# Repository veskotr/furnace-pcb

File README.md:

# Furnace Controller PCB

Hardware revisions are kept side by side:

- `Furnace_Controller_V1/` — the original 99-footprint design, last produced in June 2026.
- `Furnace_Controller_V2/` — the active 125-footprint revision, including the expanded functional-sheet hierarchy and TI footprint corrections.

Open the `Furnace_Controller.kicad_pro` inside the revision you intend to edit.
Shared third-party symbols and footprints live in `libraries/Symbols/`; each revision's
library-table files resolve these assets using project-relative paths.

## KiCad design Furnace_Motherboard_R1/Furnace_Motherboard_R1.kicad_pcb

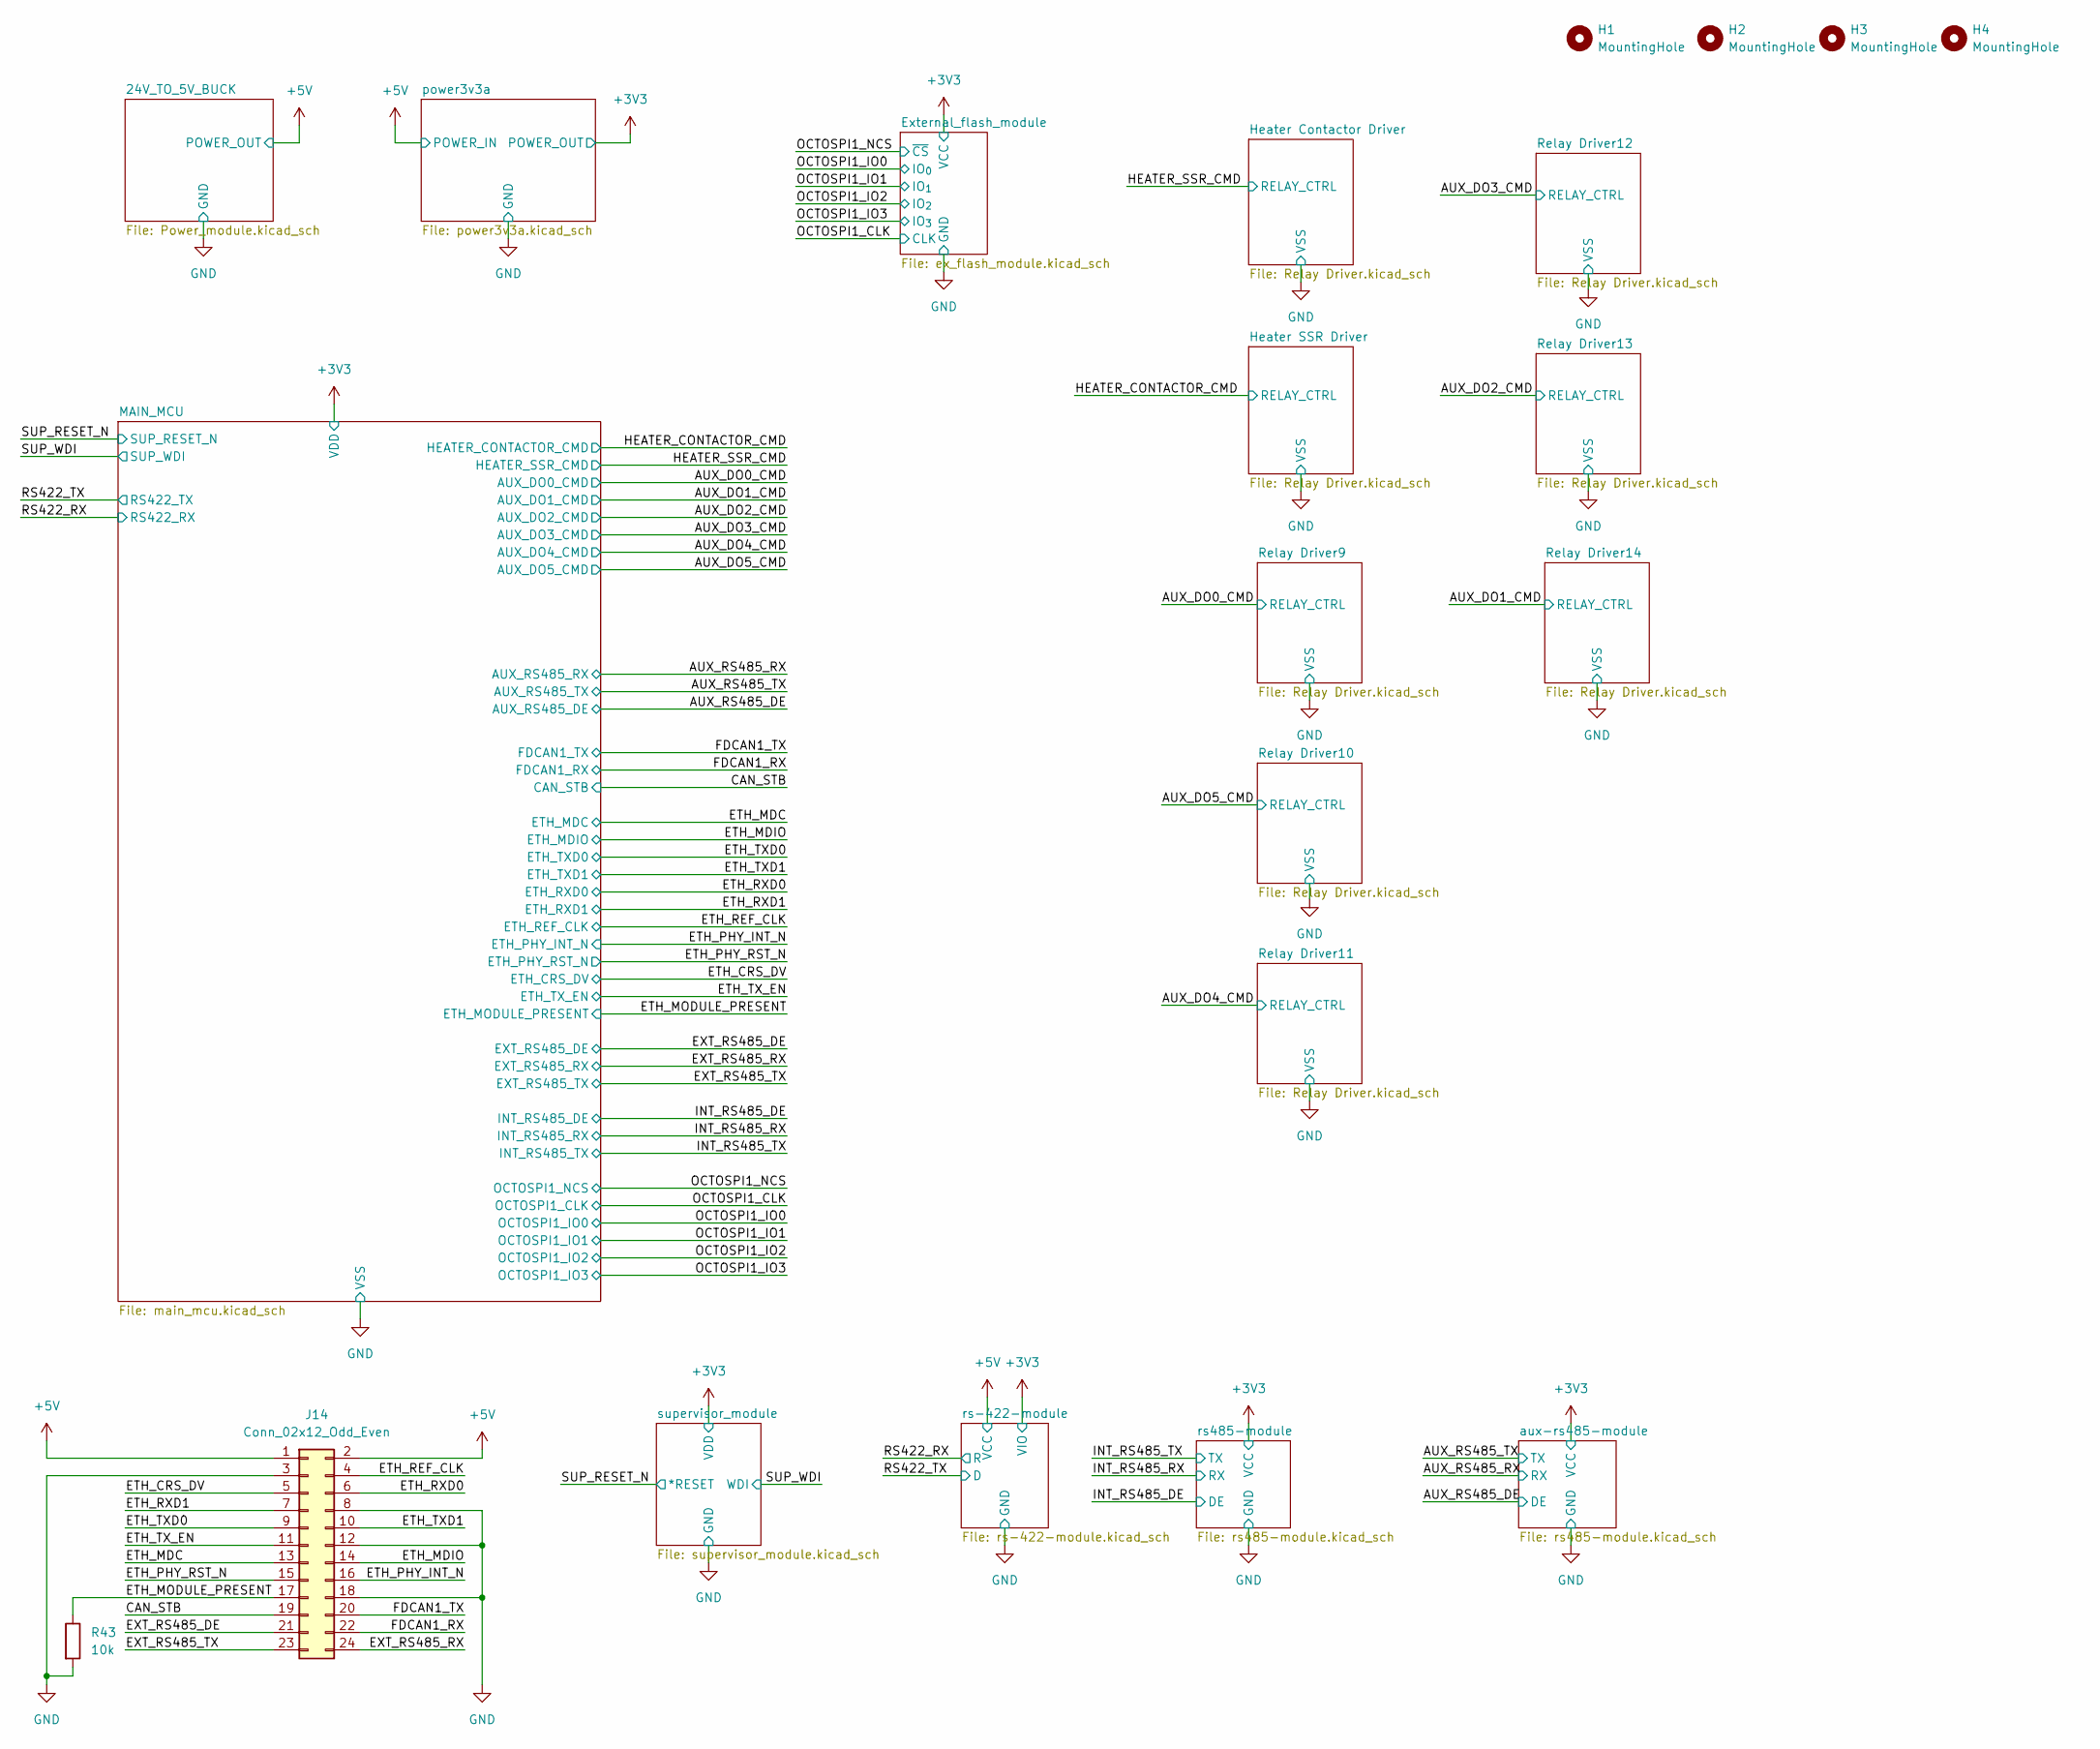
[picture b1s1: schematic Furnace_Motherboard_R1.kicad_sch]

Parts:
H1, H2, H3, H4: MountingHole; MountingHole_3.2mm_M3
J14: Conn_02x12_Odd_Even; PinSocket_2x12_P2.54mm_Vertical
R43: 10k; R_0603_1608Metric

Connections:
+5V: J14.1, J14.2; also elsewhere on the board
/CAN_STB: J14.19; also elsewhere on the board
/ETH_CRS_DV: J14.5; also elsewhere on the board
/ETH_MDC: J14.13; also elsewhere on the board
/ETH_MDIO: J14.14; also elsewhere on the board
/ETH_MODULE_PRESENT: J14.17, R43.1; also elsewhere on the board
/ETH_PHY_INT_N: J14.16; also elsewhere on the board
/ETH_PHY_RST_N: J14.15; also elsewhere on the board
/ETH_REF_CLK: J14.4; also elsewhere on the board
/ETH_RXD0: J14.6; also elsewhere on the board
/ETH_RXD1: J14.7; also elsewhere on the board
/ETH_TXD0: J14.9; also elsewhere on the board
/ETH_TXD1: J14.10; also elsewhere on the board
/ETH_TX_EN: J14.11; also elsewhere on the board
/EXT_RS485_DE: J14.21; also elsewhere on the board
/EXT_RS485_RX: J14.24; also elsewhere on the board
/EXT_RS485_TX: J14.23; also elsewhere on the board
/FDCAN1_RX: J14.22; also elsewhere on the board
/FDCAN1_TX: J14.20; also elsewhere on the board
GND: J14.3, J14.8, J14.12, J14.18, R43.2; also elsewhere on the board

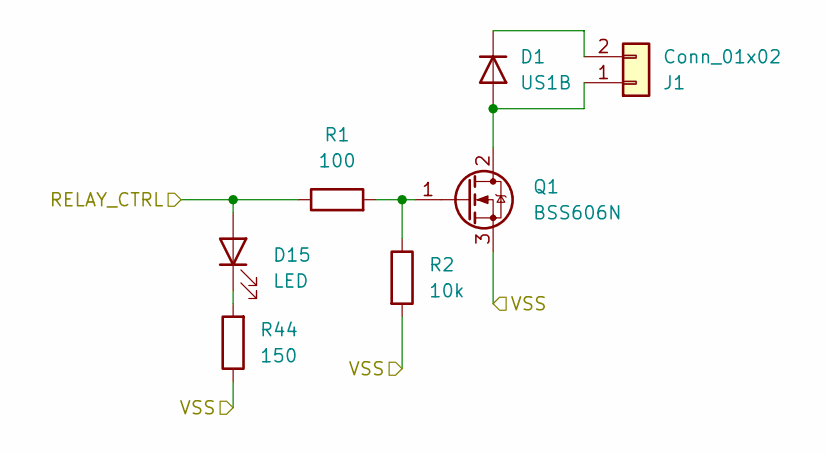
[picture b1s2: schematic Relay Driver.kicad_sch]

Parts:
D1: US1B; D_SMA
D15: LED; LED_0603_1608Metric
J1: Conn_01x02; PhoenixContact_MC_1,5_2-G-3.5_1x02_P3.50mm_Horizontal
Q1: BSS606N; Q_SOT-89
R1: 100; R_0603_1608Metric
R2: 10k; R_0603_1608Metric
R44: 150; R_0603_1608Metric

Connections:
/AUX_DO3_CMD: D15.2 (A), R1.1; also elsewhere on the board
GND: Q1.3 (S), R2.2, R44.1; also elsewhere on the board
unnamed: D1.2 (A), J1.1, Q1.2 (D)
unnamed: D1.1 (K), J1.2
unnamed: D15.1 (K), R44.2
unnamed: Q1.1 (G), R1.2, R2.1

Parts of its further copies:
D2, D6, D7, D8, D9, D10, D11: US1B; D_SMA
D16, D17, D18, D19, D20, D21, D22: LED; LED_0603_1608Metric
J2, J6, J7, J8, J9, J10, J11: Conn_01x02; PhoenixContact_MC_1,5_2-G-3.5_1x02_P3.50mm_Horizontal
Q2, Q3, Q4, Q5, Q6, Q7, Q8: BSS606N; Q_SOT-89
R3, R18, R20, R22, R24, R26, R28: 100; R_0603_1608Metric
R4, R19, R21, R23, R25, R27, R29: 10k; R_0603_1608Metric
R45, R46, R47, R48, R49, R50, R51: 150; R_0603_1608Metric

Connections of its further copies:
/AUX_DO0_CMD: D20.2 (A), R24.1; also elsewhere on the board
/AUX_DO1_CMD: D19.2 (A), R22.1; also elsewhere on the board
/AUX_DO2_CMD: D16.2 (A), R3.1; also elsewhere on the board
/AUX_DO4_CMD: D22.2 (A), R28.1; also elsewhere on the board
/AUX_DO5_CMD: D21.2 (A), R26.1; also elsewhere on the board
/HEATER_CONTACTOR_CMD: D18.2 (A), R20.1; also elsewhere on the board
/HEATER_SSR_CMD: D17.2 (A), R18.1; also elsewhere on the board
GND: Q2.3 (S), Q3.3 (S), Q4.3 (S), Q5.3 (S), Q6.3 (S), Q7.3 (S), Q8.3 (S), R4.2, R19.2, R21.2, R23.2, R25.2, R27.2, R29.2, R45.1, R46.1, R47.1, R48.1, R49.1, R50.1, R51.1; also elsewhere on the board
unnamed: D2.2 (A), J2.1, Q2.2 (D)
unnamed: D2.1 (K), J2.2
unnamed: D6.2 (A), J6.1, Q3.2 (D)
unnamed: D6.1 (K), J6.2
unnamed: D7.2 (A), J7.1, Q4.2 (D)
unnamed: D7.1 (K), J7.2
unnamed: D8.2 (A), J8.1, Q5.2 (D)
unnamed: D8.1 (K), J8.2
unnamed: D9.2 (A), J9.1, Q6.2 (D)
unnamed: D9.1 (K), J9.2
unnamed: D10.2 (A), J10.1, Q7.2 (D)
unnamed: D10.1 (K), J10.2
unnamed: D11.2 (A), J11.1, Q8.2 (D)
unnamed: D11.1 (K), J11.2
unnamed: D16.1 (K), R45.2
unnamed: D17.1 (K), R46.2
unnamed: D18.1 (K), R47.2
unnamed: D19.1 (K), R48.2
unnamed: D20.1 (K), R49.2
unnamed: D21.1 (K), R50.2
unnamed: D22.1 (K), R51.2
unnamed: Q2.1 (G), R3.2, R4.1
unnamed: Q3.1 (G), R18.2, R19.1
unnamed: Q4.1 (G), R20.2, R21.1
unnamed: Q5.1 (G), R22.2, R23.1
unnamed: Q6.1 (G), R24.2, R25.1
unnamed: Q7.1 (G), R26.2, R27.1
unnamed: Q8.1 (G), R28.2, R29.1

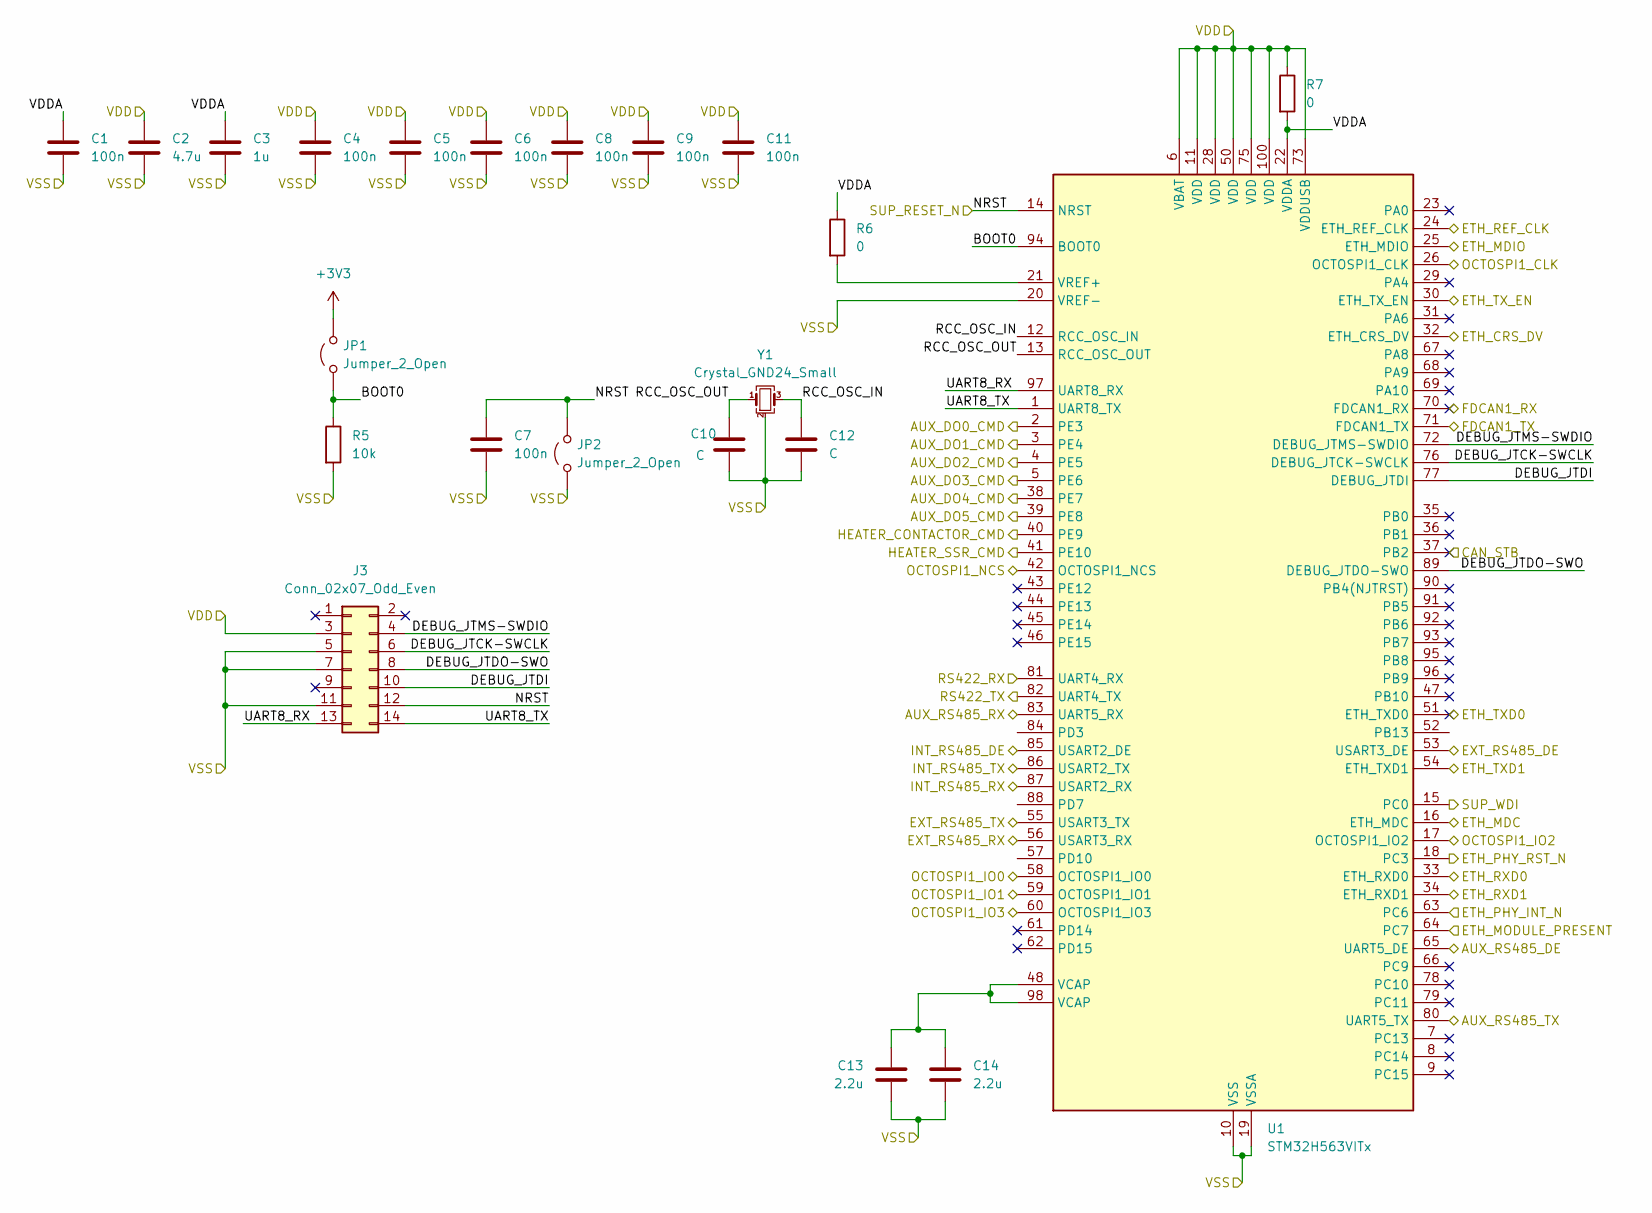
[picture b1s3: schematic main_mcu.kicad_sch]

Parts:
C1, C4, C5, C6, C7, C8, C9, C11: 100n; C_0603_1608Metric
C2: 4.7u; C_0805_2012Metric
C3: 1u; C_0603_1608Metric
C10, C12: C; C_0603_1608Metric
C13, C14: 2.2u; C_0805_2012Metric
J3: Conn_02x07_Odd_Even; PinHeader_2x07_P1.27mm_Vertical
JP1, JP2: Jumper_2_Open; TestPoint_2Pads_Pitch2.54mm_Drill0.8mm
R5: 10k; R_0603_1608Metric
R6, R7: 0; R_0603_1608Metric
U1: STM32H563VITx; LQFP-100_14x14mm_P0.5mm
Y1: Crystal_GND24_Small; Crystal_SMD_3225-4Pin_3.2x2.5mm

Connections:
+3V3: C2.1, C4.1, C5.1, C6.1, C8.1, C9.1, C11.1, J3.3, JP1.2 (B), R7.1, U1.6 (VBAT), U1.11 (VDD), U1.28 (VDD), U1.50 (VDD), U1.73 (VDDUSB), U1.75 (VDD), U1.100 (VDD); also elsewhere on the board
/AUX_DO0_CMD: U1.2 (PE3); also elsewhere on the board
/AUX_DO1_CMD: U1.3 (PE4); also elsewhere on the board
/AUX_DO2_CMD: U1.4 (PE5); also elsewhere on the board
/AUX_DO3_CMD: U1.5 (PE6); also elsewhere on the board
/AUX_DO4_CMD: U1.38 (PE7); also elsewhere on the board
/AUX_DO5_CMD: U1.39 (PE8); also elsewhere on the board
/AUX_RS485_DE: U1.65 (UART5_DE); also elsewhere on the board
/AUX_RS485_RX: U1.83 (UART5_RX); also elsewhere on the board
/AUX_RS485_TX: U1.80 (UART5_TX); also elsewhere on the board
/CAN_STB: U1.37 (PB2); also elsewhere on the board
/ETH_CRS_DV: U1.32 (ETH_CRS_DV); also elsewhere on the board
/ETH_MDC: U1.16 (ETH_MDC); also elsewhere on the board
/ETH_MDIO: U1.25 (ETH_MDIO); also elsewhere on the board
/ETH_MODULE_PRESENT: U1.64 (PC7); also elsewhere on the board
/ETH_PHY_INT_N: U1.63 (PC6); also elsewhere on the board
/ETH_PHY_RST_N: U1.18 (PC3); also elsewhere on the board
/ETH_REF_CLK: U1.24 (ETH_REF_CLK); also elsewhere on the board
/ETH_RXD0: U1.33 (ETH_RXD0); also elsewhere on the board
/ETH_RXD1: U1.34 (ETH_RXD1); also elsewhere on the board
/ETH_TXD0: U1.51 (ETH_TXD0); also elsewhere on the board
/ETH_TXD1: U1.54 (ETH_TXD1); also elsewhere on the board
/ETH_TX_EN: U1.30 (ETH_TX_EN); also elsewhere on the board
/EXT_RS485_DE: U1.53 (USART3_DE); also elsewhere on the board
/EXT_RS485_RX: U1.56 (USART3_RX); also elsewhere on the board
/EXT_RS485_TX: U1.55 (USART3_TX); also elsewhere on the board
/FDCAN1_RX: U1.70 (FDCAN1_RX); also elsewhere on the board
/FDCAN1_TX: U1.71 (FDCAN1_TX); also elsewhere on the board
/HEATER_CONTACTOR_CMD: U1.40 (PE9); also elsewhere on the board
/HEATER_SSR_CMD: U1.41 (PE10); also elsewhere on the board
/INT_RS485_DE: U1.85 (USART2_DE); also elsewhere on the board
/INT_RS485_RX: U1.87 (USART2_RX); also elsewhere on the board
/INT_RS485_TX: U1.86 (USART2_TX); also elsewhere on the board
/MAIN_MCU/BOOT0: JP1.1 (A), R5.1, U1.94 (BOOT0)
/MAIN_MCU/DEBUG_JTCK-SWCLK: J3.6, U1.76 (DEBUG_JTCK-SWCLK)
/MAIN_MCU/DEBUG_JTDI: J3.10, U1.77 (DEBUG_JTDI)
/MAIN_MCU/DEBUG_JTDO-SWO: J3.8, U1.89 (DEBUG_JTDO-SWO)
/MAIN_MCU/DEBUG_JTMS-SWDIO: J3.4, U1.72 (DEBUG_JTMS-SWDIO)
/MAIN_MCU/RCC_OSC_IN: C12.1, U1.12 (RCC_OSC_IN), Y1.3
/MAIN_MCU/RCC_OSC_OUT: C10.1, U1.13 (RCC_OSC_OUT), Y1.1
/MAIN_MCU/UART8_RX: J3.13, U1.97 (UART8_RX)
/MAIN_MCU/UART8_TX: J3.14, U1.1 (UART8_TX)
/MAIN_MCU/VDDA: C1.1, C3.1, R6.1, R7.2, U1.22 (VDDA)
/OCTOSPI1_CLK: U1.26 (OCTOSPI1_CLK); also elsewhere on the board
/OCTOSPI1_IO0: U1.58 (OCTOSPI1_IO0); also elsewhere on the board
/OCTOSPI1_IO1: U1.59 (OCTOSPI1_IO1); also elsewhere on the board
/OCTOSPI1_IO2: U1.17 (OCTOSPI1_IO2); also elsewhere on the board
/OCTOSPI1_IO3: U1.60 (OCTOSPI1_IO3); also elsewhere on the board
/OCTOSPI1_NCS: U1.42 (OCTOSPI1_NCS); also elsewhere on the board
/RS422_RX: U1.81 (UART4_RX); also elsewhere on the board
/RS422_TX: U1.82 (UART4_TX); also elsewhere on the board
/SUP_RESET_N: C7.1, J3.12, JP2.2 (B), U1.14 (NRST); also elsewhere on the board
/SUP_WDI: U1.15 (PC0); also elsewhere on the board
GND: C1.2, C2.2, C3.2, C4.2, C5.2, C6.2, C7.2, C8.2, C9.2, C10.2, C11.2, C12.2, C13.2, C14.2, J3.5, J3.7, J3.11, JP2.1 (A), R5.2, U1.10 (VSS), U1.19 (VSSA), U1.20 (VREF-), U1.27 (VSS), U1.49 (VSS), U1.74 (VSS), U1.99 (VSS), Y1.2 (G), Y1.4 (G); also elsewhere on the board
unnamed: C13.1, C14.1, U1.48 (VCAP), U1.98 (VCAP)
unnamed: R6.2, U1.21 (VREF+)

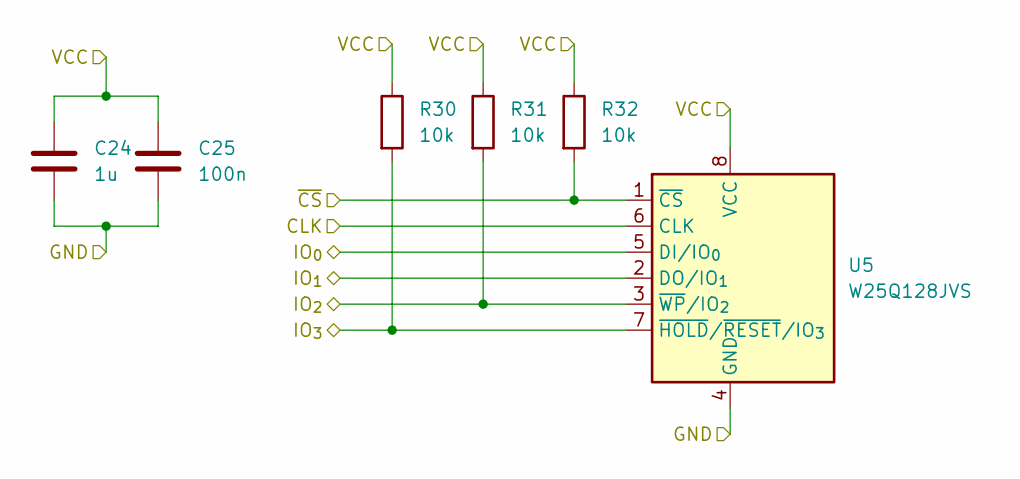
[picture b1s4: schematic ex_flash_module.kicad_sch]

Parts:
C24: 1u; C_0603_1608Metric
C25: 100n; C_0603_1608Metric
R30, R31, R32: 10k; R_0603_1608Metric
U5: W25Q128JVS; SOIC-8_5.3x5.3mm_P1.27mm

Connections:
+3V3: C24.1, C25.1, R30.1, R31.1, R32.1, U5.8 (VCC); also elsewhere on the board
/OCTOSPI1_CLK: U5.6 (CLK); also elsewhere on the board
/OCTOSPI1_IO0: U5.5 (DI/IO_{0}); also elsewhere on the board
/OCTOSPI1_IO1: U5.2 (DO/IO_{1}); also elsewhere on the board
/OCTOSPI1_IO2: R31.2, U5.3 (~WP/IO_{2}); also elsewhere on the board
/OCTOSPI1_IO3: R30.2, U5.7 (~HOLD/~RESET/IO_{3}); also elsewhere on the board
/OCTOSPI1_NCS: R32.2, U5.1 (~CS); also elsewhere on the board
GND: C24.2, C25.2, U5.4 (GND); also elsewhere on the board

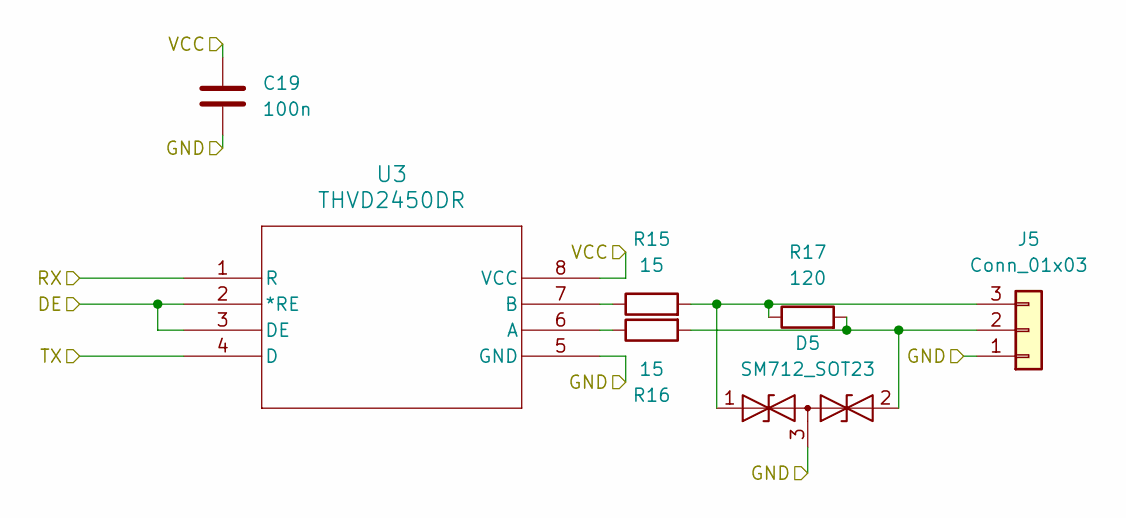
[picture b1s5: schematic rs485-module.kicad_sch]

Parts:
C19: 100n; C_0603_1608Metric
D5: SM712_SOT23; SOT-23
J5: Conn_01x03; PhoenixContact_MC_1,5_3-G-3.5_1x03_P3.50mm_Horizontal
R15, R16: 15; R_0603_1608Metric
R17: 120; R_0603_1608Metric
U3: THVD2450DR; SOIC-8_3.9x4.9mm_P1.27mm

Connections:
+3V3: C19.1, U3.8 (VCC); also elsewhere on the board
/INT_RS485_DE: U3.2 (*RE), U3.3 (DE); also elsewhere on the board
/INT_RS485_RX: U3.1 (R); also elsewhere on the board
/INT_RS485_TX: U3.4 (D); also elsewhere on the board
GND: C19.2, D5.3 (common), J5.1, U3.5 (GND); also elsewhere on the board
unnamed: D5.1 (A1), J5.3, R15.2, R17.1
unnamed: D5.2 (A2), J5.2, R16.2, R17.2
unnamed: R16.1, U3.6 (A)
unnamed: R15.1, U3.7 (B)

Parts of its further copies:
C29: 100n; C_0603_1608Metric
D12: SM712_SOT23; SOT-23
J12: Conn_01x03; PhoenixContact_MC_1,5_3-G-3.5_1x03_P3.50mm_Horizontal
R35, R36: 15; R_0603_1608Metric
R37: 120; R_0603_1608Metric
U7: THVD2450DR; SOIC-8_3.9x4.9mm_P1.27mm

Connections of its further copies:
+3V3: C29.1, U7.8 (VCC); also elsewhere on the board
/AUX_RS485_DE: U7.2 (*RE), U7.3 (DE); also elsewhere on the board
/AUX_RS485_RX: U7.1 (R); also elsewhere on the board
/AUX_RS485_TX: U7.4 (D); also elsewhere on the board
GND: C29.2, D12.3 (common), J12.1, U7.5 (GND); also elsewhere on the board
unnamed: D12.1 (A1), J12.3, R35.2, R37.1
unnamed: D12.2 (A2), J12.2, R36.2, R37.2
unnamed: R36.1, U7.6 (A)
unnamed: R35.1, U7.7 (B)

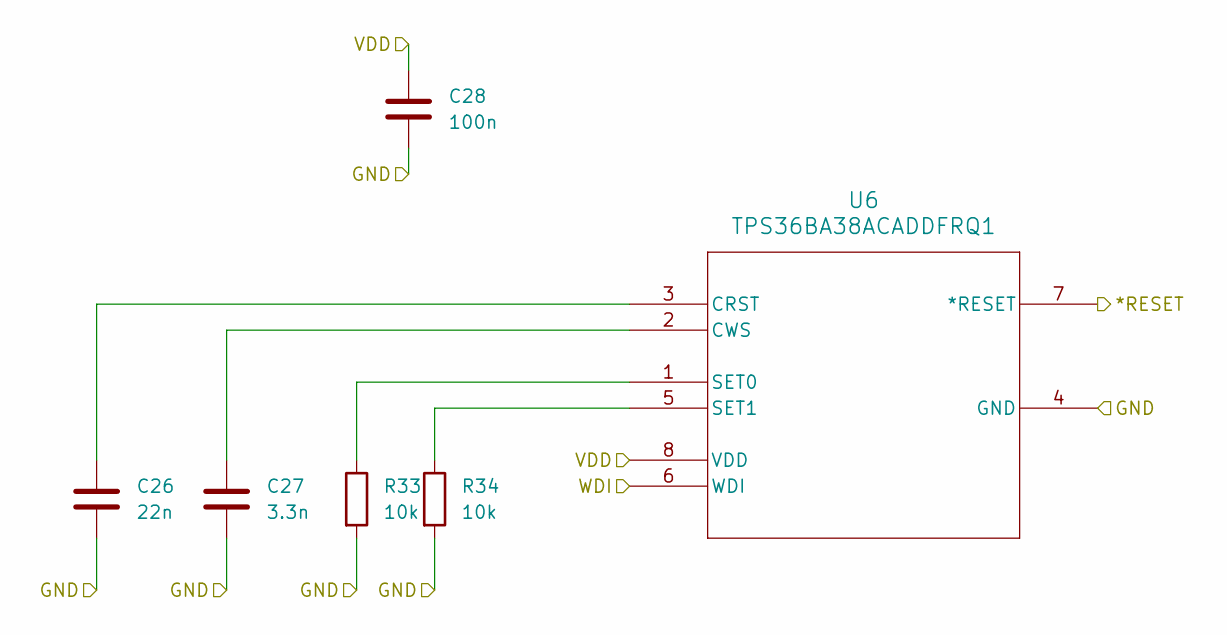
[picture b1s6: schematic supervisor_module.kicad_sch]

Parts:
C26: 22n; C_0603_1608Metric
C27: 3.3n; C_0603_1608Metric
C28: 100n; C_0603_1608Metric
R33, R34: 10k; R_0603_1608Metric
U6: TPS36BA38ACADDFRQ1; SOT-23-THIN-8_DDF_TEX

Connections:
+3V3: C28.1, U6.8 (VDD); also elsewhere on the board
/SUP_RESET_N: U6.7 (*RESET); also elsewhere on the board
/SUP_WDI: U6.6 (WDI); also elsewhere on the board
GND: C26.2, C27.2, C28.2, R33.2, R34.2, U6.4 (GND); also elsewhere on the board
unnamed: C26.1, U6.3 (CRST)
unnamed: C27.1, U6.2 (CWS)
unnamed: R33.1, U6.1 (SET0)
unnamed: R34.1, U6.5 (SET1)

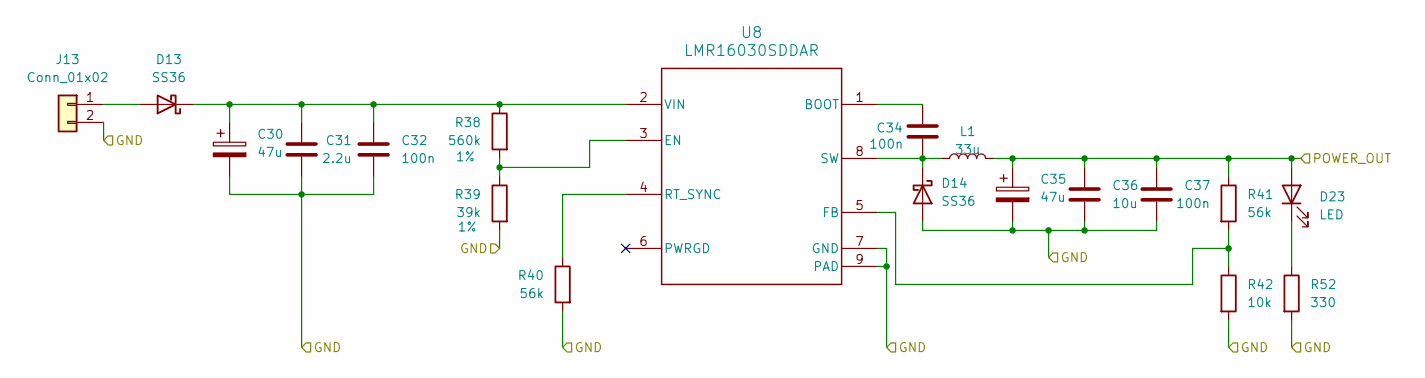
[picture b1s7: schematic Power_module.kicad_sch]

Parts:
C30, C35: 47u; CP_Radial_D6.3mm_P2.50mm
C31: 2.2u; C_0805_2012Metric
C32, C34, C37: 100n; C_0603_1608Metric
C36: 10u; C_0805_2012Metric
D13, D14: SS36; D_SMA
D23: LED; LED_0603_1608Metric
J13: Conn_01x02; PhoenixContact_MC_1,5_2-G-3.5_1x02_P3.50mm_Horizontal
L1: 33u; L_6.3x6.3_H3
R38: 560k; R_0603_1608Metric; Tolerance 1%
R39: 39k; R_0603_1608Metric; Tolerance 1%
R40, R41: 56k; R_0603_1608Metric
R42: 10k; R_0603_1608Metric
R52: 330; R_0603_1608Metric
U8: LMR16030SDDAR; SOIC-8-1EP_3.9x4.9mm_P1.27mm_EP2.29x3mm

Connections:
+5V: C35.1, C36.1, C37.1, D23.2 (A), L1.2, R41.1; also elsewhere on the board
GND: C30.2, C31.2, C32.2, C35.2, C36.2, C37.2, D14.2 (A), J13.2, R39.2, R40.2, R42.2, R52.2, U8.7 (GND), U8.9 (PAD); also elsewhere on the board
unnamed: D13.2 (A), J13.1
unnamed: C30.1, C31.1, C32.1, D13.1 (K), R38.1, U8.2 (VIN)
unnamed: C34.2, D14.1 (K), L1.1, U8.8 (SW)
unnamed: D23.1 (K), R52.1
unnamed: C34.1, U8.1 (BOOT)
unnamed: R38.2, R39.1, U8.3 (EN)
unnamed: R41.2, R42.1, U8.5 (FB)
unnamed: R40.1, U8.4 (RT_SYNC)

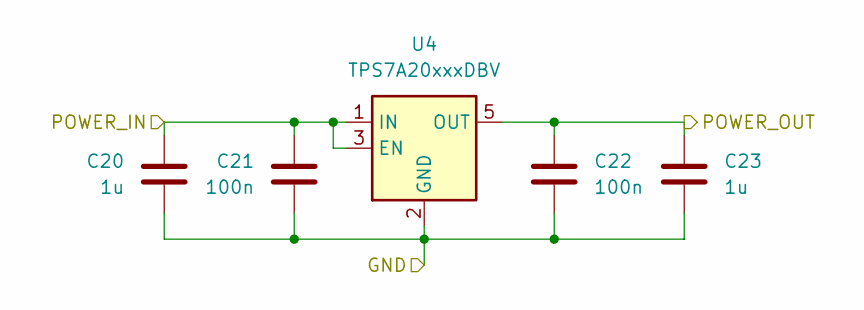
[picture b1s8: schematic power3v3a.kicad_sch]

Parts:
C20, C23: 1u; C_0603_1608Metric
C21, C22: 100n; C_0603_1608Metric
U4: TPS7A20xxxDBV; SOT-23-5

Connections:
+3V3: C22.1, C23.1, U4.5 (OUT); also elsewhere on the board
+5V: C20.1, C21.1, U4.1 (IN), U4.3 (EN); also elsewhere on the board
GND: C20.2, C21.2, C22.2, C23.2, U4.2 (GND); also elsewhere on the board

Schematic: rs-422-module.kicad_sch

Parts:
C15, C16: 100n; C_0603_1608Metric
C17, C18: 1u; C_0805_2012Metric
D3, D4: SM712_SOT23; SOT-23
J4: Conn_01x05; PhoenixContact_MC_1,5_5-G-3.5_1x05_P3.50mm_Horizontal
R8, R10, R11: 10k; R_0603_1608Metric
R9: 0; R_0603_1608Metric
R12: 120; R_0603_1608Metric
R13, R14: 15; R_0603_1608Metric
U2: PTHVD2452VDR; SOIC-14_L8.7-W3.9-P1.27-LS6.0-BL

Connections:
+3V3: C15.1, C17.1, R8.1, R10.1, U2.1 (VIO); also elsewhere on the board
+5V: C16.1, C18.1, U2.14 (VCC); also elsewhere on the board
/RS422_RX: U2.2 (R); also elsewhere on the board
/RS422_TX: U2.5 (D); also elsewhere on the board
/rs-422-module/A: D3.1 (A1), J4.5, R12.1, U2.12 (A)
/rs-422-module/B: D3.2 (A2), J4.4, R12.2, U2.11 (B)
/rs-422-module/Y: D4.2 (A2), J4.2, R13.1
/rs-422-module/Z: D4.1 (A1), J4.3, R14.1
GND: C15.2, C16.2, C17.2, C18.2, D3.3 (common), D4.3 (common), J4.1, R9.2, R11.2, U2.6 (GND); also elsewhere on the board
unnamed: R11.1, U2.3 (*RE)
unnamed: R10.2, U2.4 (DE)
unnamed: R8.2, R9.1, U2.8 (SLR)
unnamed: R13.2, U2.9 (Y)
unnamed: R14.2, U2.10 (Z)

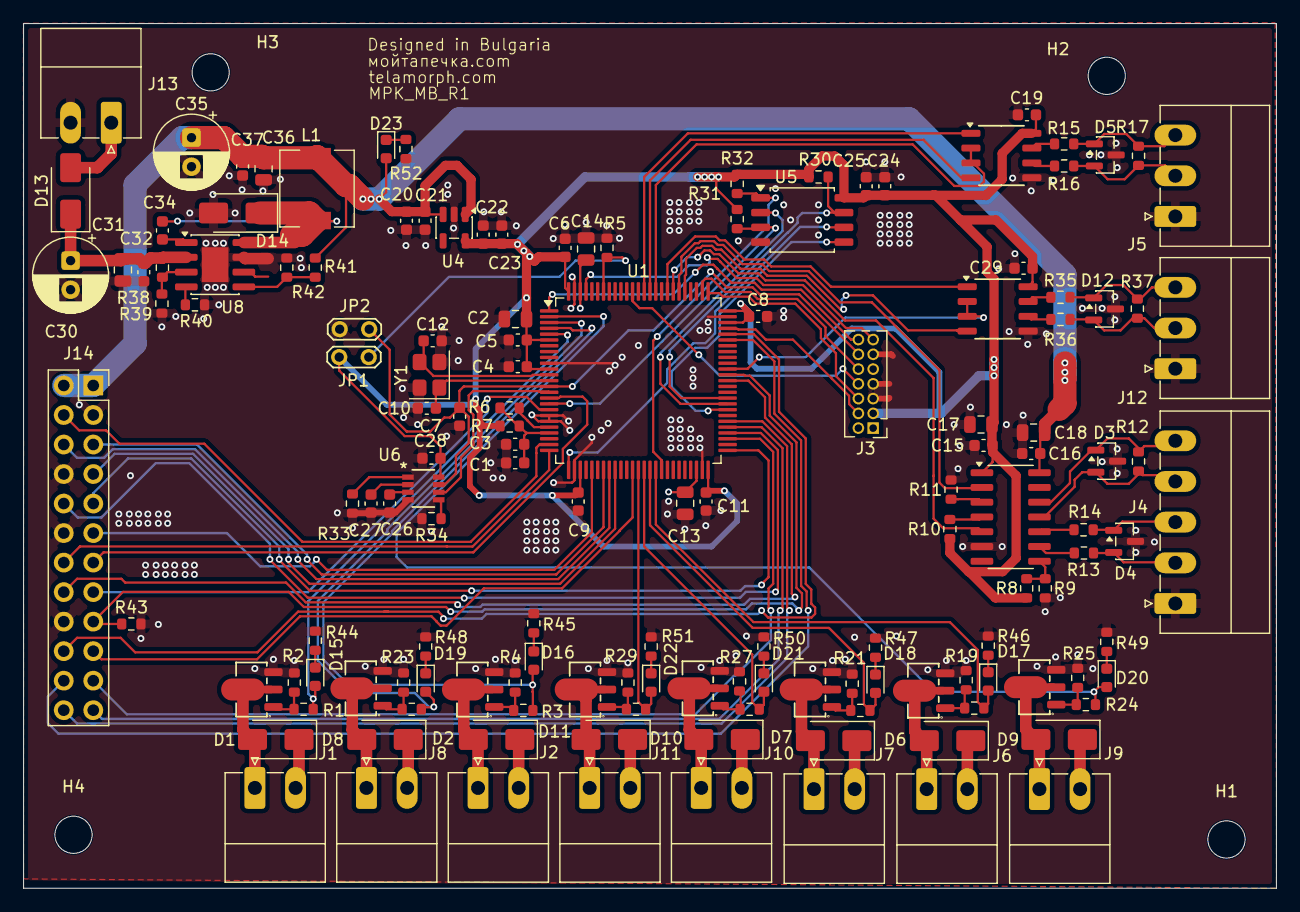
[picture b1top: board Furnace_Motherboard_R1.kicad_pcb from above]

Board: 4 copper layers, 107.8 x 74.4 mm, 149 parts (0 on the bottom side), 118 nets.

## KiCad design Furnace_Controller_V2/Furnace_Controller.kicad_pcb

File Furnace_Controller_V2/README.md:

# Furnace Controller V2

Open `Furnace_Controller.kicad_pro` as the project entry point.

The root schematic is the system sheet. Functional sheets are named by their
role (power conversion, communications, supervision, I/O, Ethernet, and relay
drivers). Repeated relay and 3.3 V regulator channels intentionally share a
single child-sheet source.

Project-local TI symbols and footprints are declared in `sym-lib-table` and
`fp-lib-table`; their source files live in `../libraries/Symbols/`. Child
schematics live in `sheets/`; generated Gerbers and assembly outputs live in
`fabrication/`, while PDFs and 3D exports live in `documentation/`.

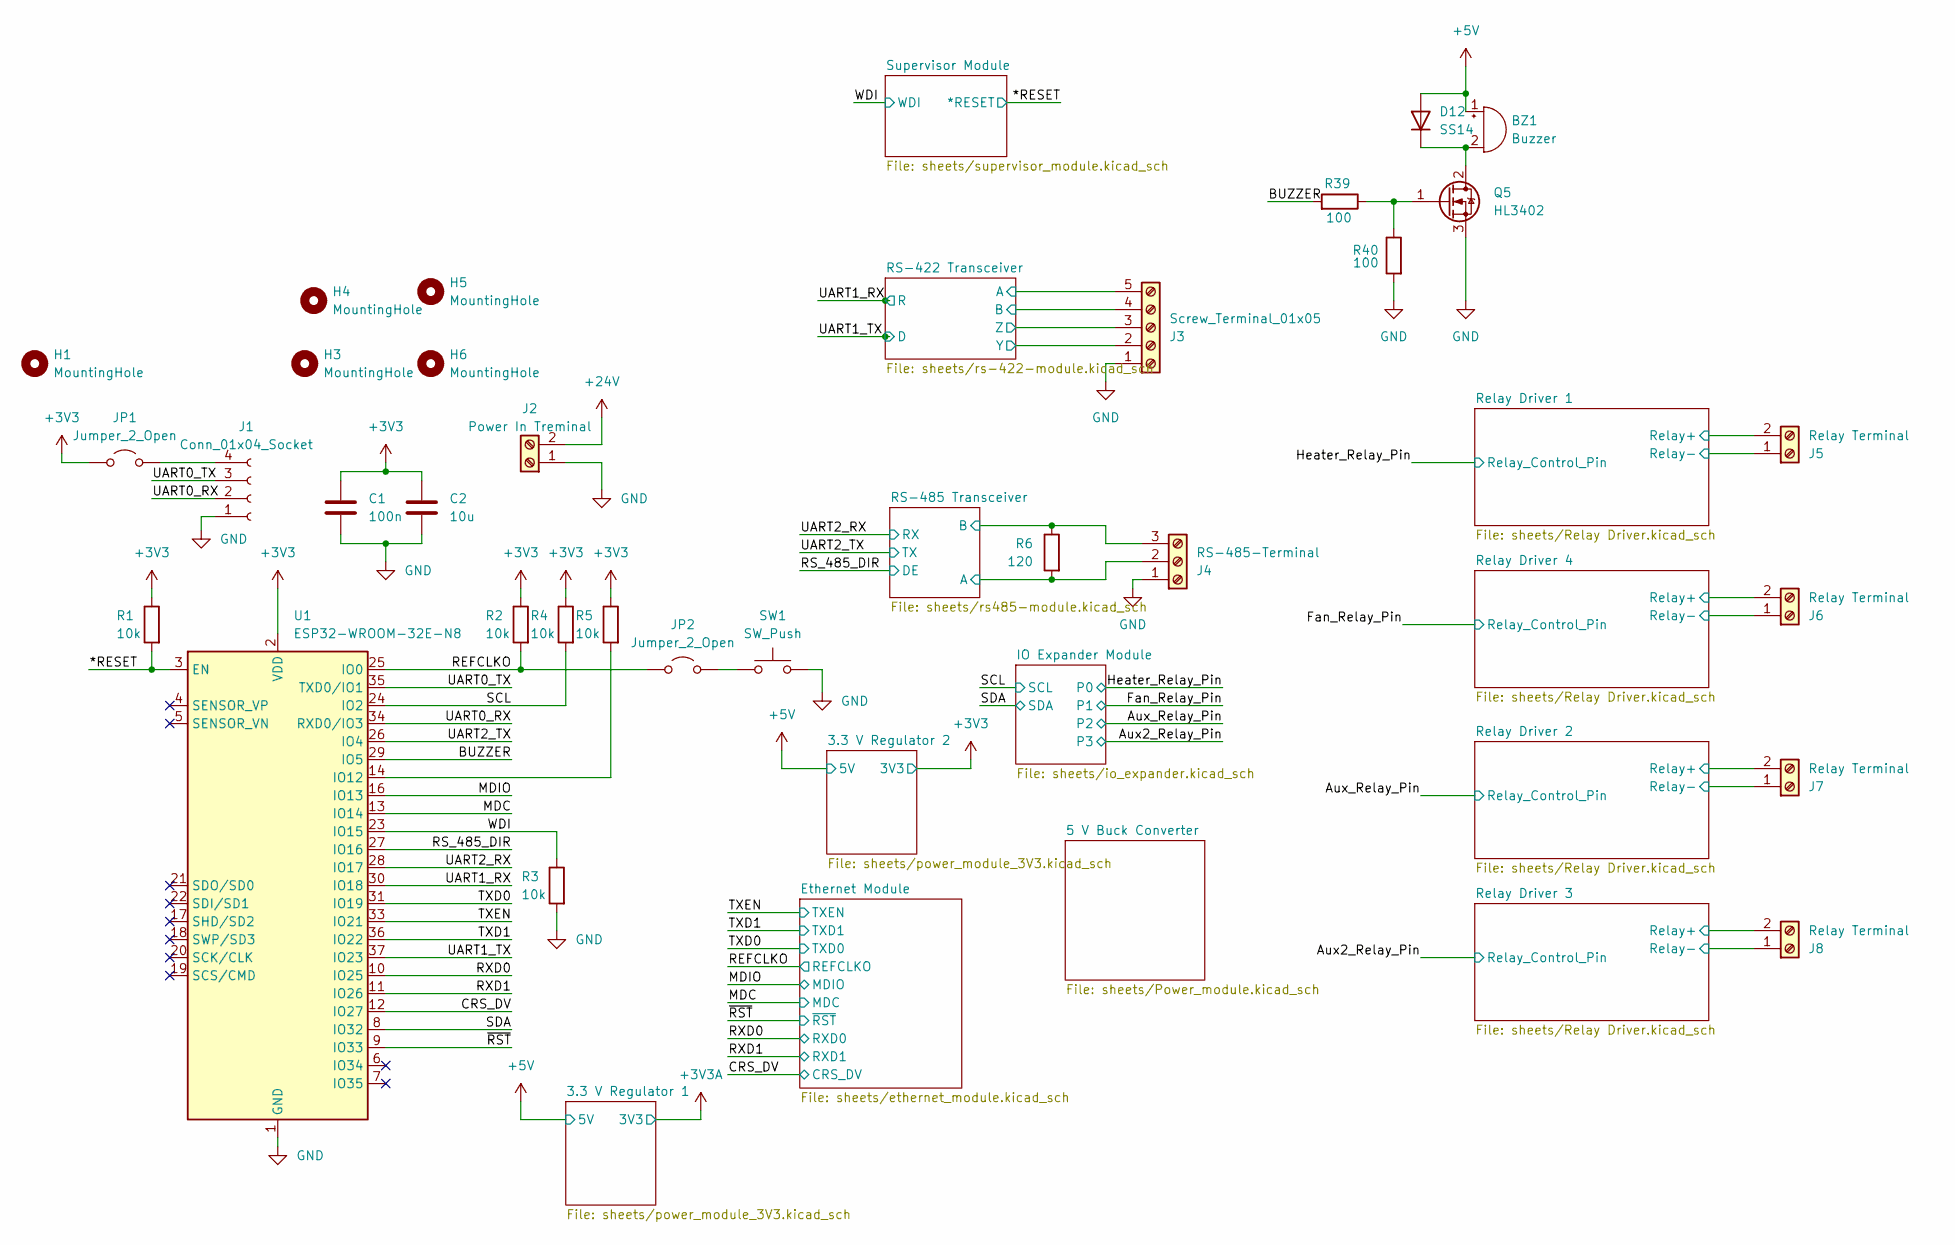
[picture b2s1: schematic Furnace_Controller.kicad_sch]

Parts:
BZ1: Buzzer; Buzzer_15x7.5RM7.6
C1: 100n; C_0603_1608Metric
C2: 10u; C_0805_2012Metric
D12: SS14; D_SOD-123
H1, H3, H4, H6: MountingHole; MountingHole_3.2mm_M3
H5: MountingHole; MountingHole_2.2mm_M2
J1: Conn_01x04_Socket; PinHeader_1x04_P2.54mm_Vertical
J2: Power In Treminal; PhoenixContact_MC_1,5_2-G-3.5_1x02_P3.50mm_Horizontal
J3: Screw_Terminal_01x05; PhoenixContact_MC_1,5_5-G-3.5_1x05_P3.50mm_Horizontal
J4: RS-485-Terminal; PhoenixContact_MC_1,5_3-G-3.5_1x03_P3.50mm_Horizontal
J5, J6, J7, J8: Relay Terminal; PhoenixContact_MC_1,5_2-G-3.5_1x02_P3.50mm_Horizontal
JP1, JP2: Jumper_2_Open; TestPoint_2Pads_Pitch2.54mm_Drill0.8mm
Q5: HL3402; Q_SOT-23
R1, R2, R3, R4, R5: 10k; R_0603_1608Metric
R6: 120; R_0603_1608Metric
R39, R40: 100; R_0603_1608Metric
SW1: SW_Push; SW_PUSH_6mm_H4.3mm
U1: ESP32-WROOM-32E-N8; ESP32-WROOM-32

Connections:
+3V3: C1.1, C2.1, JP1.1 (A), R1.1, R2.1, R4.1, R5.1, U1.2 (VDD); also elsewhere on the board
+5V: BZ1.1 (+), D12.2 (A); also elsewhere on the board
+24V: J2.2, J5.2, J6.2, J7.2, J8.2; also elsewhere on the board
/*RESET: R1.2, U1.3 (EN); also elsewhere on the board
/BUZZER: R39.2, U1.29 (IO5)
/CRS_DV: U1.12 (IO27); also elsewhere on the board
/MDC: U1.13 (IO14); also elsewhere on the board
/MDIO: U1.16 (IO13); also elsewhere on the board
/REFCLKO: JP2.1 (A), R2.2, U1.25 (IO0); also elsewhere on the board
/RS-422-module/A: J3.5; also elsewhere on the board
/RS-422-module/B: J3.4; also elsewhere on the board
/RS-422-module/Y: J3.2; also elsewhere on the board
/RS-422-module/Z: J3.3; also elsewhere on the board
/RS_485_DIR: U1.27 (IO16); also elsewhere on the board
/RXD0: U1.10 (IO25); also elsewhere on the board
/RXD1: U1.11 (IO26); also elsewhere on the board
/Relay Driver1/Relay-: J6.1; also elsewhere on the board
/Relay Driver2/Relay-: J7.1; also elsewhere on the board
/Relay Driver3/Relay-: J8.1; also elsewhere on the board
/Relay Driver/Relay-: J5.1; also elsewhere on the board
/SCL: R4.2, U1.24 (IO2); also elsewhere on the board
/SDA: U1.8 (IO32); also elsewhere on the board
/TXD0: U1.31 (IO19); also elsewhere on the board
/TXD1: U1.36 (IO22); also elsewhere on the board
/TXEN: U1.33 (IO21); also elsewhere on the board
/UART0_RX: J1.2, U1.34 (RXD0/IO3)
/UART0_TX: J1.3, U1.35 (TXD0/IO1)
/UART1_RX: U1.30 (IO18); also elsewhere on the board
/UART1_TX: U1.37 (IO23); also elsewhere on the board
/UART2_RX: U1.28 (IO17); also elsewhere on the board
/UART2_TX: U1.26 (IO4); also elsewhere on the board
/WDI: R3.1, U1.23 (IO15); also elsewhere on the board
/rs485-module/A: J4.2, R6.2; also elsewhere on the board
/rs485-module/B: J4.3, R6.1; also elsewhere on the board
/~RST: U1.9 (IO33); also elsewhere on the board
GND: C1.2, C2.2, J1.1, J2.1, J3.1, J4.1, Q5.3 (S), R3.2, R40.2, SW1.2, U1.1 (GND), U1.15 (GND), U1.38 (GND), U1.39 (GND); also elsewhere on the board
unnamed: BZ1.2 (-), D12.1 (K), Q5.2 (D)
unnamed: J1.4, JP1.2 (B)
unnamed: JP2.2 (B), SW1.1
unnamed: Q5.1 (G), R39.1, R40.1
unnamed: R5.2, U1.14 (IO12)
